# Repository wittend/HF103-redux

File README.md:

# NOTE: Just testing this REPO right now. - It may not work correctly!!
# HF103-redux
### A rework of an HF SDR using USB3 derived from a design developed by Oskar Stella, IK1XPV.
This variant is meant as a straw-man starting point for discussion of project options by members of the HamSCI and TAPR groups for scientific data-collection applications.  

It is a re-capture of design elements drawn from  Oskar's HF103, BBRF103, and other sources into a schematic drawn in KiCad.

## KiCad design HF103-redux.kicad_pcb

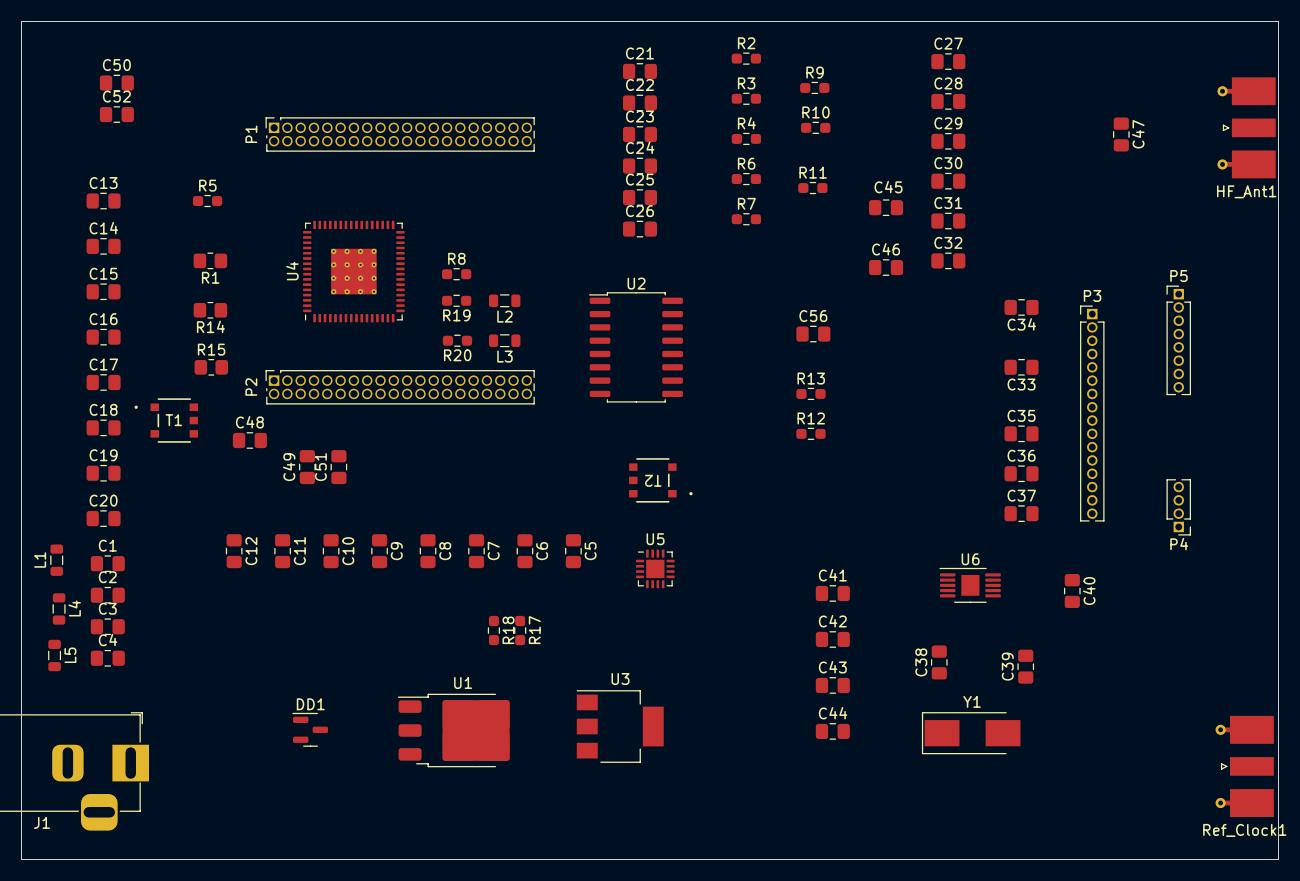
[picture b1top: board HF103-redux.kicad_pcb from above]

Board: 2 copper layers, 120.0 x 80.0 mm, 95 parts (0 on the bottom side), 75 nets, no tracks yet.

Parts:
C1, C4: 56pF; C_0805_2012Metric_Pad1.18x1.45mm_HandSolder
C2, C3: 150pF; C_0805_2012Metric_Pad1.18x1.45mm_HandSolder
C5, C6, C10, C11, C47: 100nF; C_0805_2012Metric_Pad1.18x1.45mm_HandSolder
C7, C8, C12: 1uF; C_0805_2012Metric_Pad1.18x1.45mm_HandSolder
C9: 10uF; C_0805_2012Metric_Pad1.18x1.45mm_HandSolder
C13, C14, C15, C16, C17, C18, C19, C20: C; C_0805_2012Metric_Pad1.18x1.45mm_HandSolder
C21, C22, C23, C24, C25, C26, C27, C28, C29, C30, C31, C32, C33, C34, C35, C36, C37, C42, C44, C46: 100pf; C_0805_2012Metric_Pad1.18x1.45mm_HandSolder
C38, C39: ? pF; C_0805_2012Metric_Pad1.18x1.45mm_HandSolder
C40: 1 nF; C_0805_2012Metric_Pad1.18x1.45mm_HandSolder
C41, C43, C45, C52, C56: 100nf; C_0805_2012Metric_Pad1.18x1.45mm_HandSolder
C48, C49: 8p2; C_0805_2012Metric_Pad1.18x1.45mm_HandSolder
C50: 10nf; C_0805_2012Metric_Pad1.18x1.45mm_HandSolder
C51: 4p2; C_0805_2012Metric_Pad1.18x1.45mm_HandSolder
DD1: BAV99; SOT-23
HF_Ant1: Conn_Coaxial; SMA_Molex_73251-2120_EdgeMount_Horizontal
J1: Barrel_Jack; BarrelJack_Horizontal
L1, L5: 390nH; L_0805_2012Metric
L2, L3: 68nH; L_0805_2012Metric
L4: 470nH; L_0805_2012Metric
P1, P2: Conn_02x20_Odd_Even; PinSocket_2x20_P1.27mm_Vertical
P3: Conn_01x16; PinHeader_1x16_P1.27mm_Vertical
P4: Conn_01x04; PinHeader_1x04_P1.27mm_Vertical
P5: Conn_01x08; PinHeader_1x08_P1.27mm_Vertical
R1, R14, R15: 100; R_0805_2012Metric_Pad1.20x1.40mm_HandSolder
R2, R4, R5, R6, R7, R8, R9, R10, R11: 1k; R_0603_1608Metric_Pad0.98x0.95mm_HandSolder
R3: 10k; R_0603_1608Metric_Pad0.98x0.95mm_HandSolder
R12, R13: 100; R_0603_1608Metric_Pad0.98x0.95mm_HandSolder
R17, R18, R19, R20: TBD; R_0603_1608Metric_Pad0.98x0.95mm_HandSolder
Ref_Clock1: Conn_Coaxial; SMA_Molex_73251-2120_EdgeMount_Horizontal
T1, T2: ETC1-1T-2TR; ETC1-1-13TR_MCM
U1: AMS1117CD-1.8; TO-252-3_TabPin2
U2: 74CBTLV3253; SO-16_5.3x10.2mm_P1.27mm
U3: AP7361C-33E; SOT-223-3_TabPin2
U4: LTC2208CUP-14-PBF; QFN-64-1EP_9x9mm_P0.5mm_EP4.35x4.35mm_ThermalVias
U5: LTC6400CUD-20-PBF; QFN-16-1EP_3x3mm_P0.5mm_EP1.75x1.75mm
U6: SI5351A-B-GT; MSOP-10-1EP_3x3mm_P0.5mm_EP1.73x1.98mm
Y1: 27 MHz; Crystal_SMD_0603-2Pin_6.0x3.5mm_HandSoldering

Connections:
+1V8: C6.1, C7.1, U1.2 (VO)
AIN+: R19.1, U4.8 (AIN+)
AIN-: R20.1, U4.9 (AIN-)
ATT CLK: C32.1, R6.2
ATT DATA: C31.1, R7.2
ATT LE: C33.1, P3.8, R4.2
CLK0: C51.2, U6.10 (CLK0)
D0: P2.38, U4.44 (D7+/DA0)
D1: P2.36, U4.45 (D8-/DA1)
D2: P2.34, U4.46 (D8+/DA2)
D3: P2.32, U4.47 (D9-/DA3)
D4: P2.30, U4.48 (D9+/DA4)
D5: P2.28, U4.51 (D10-/DA5)
D6: P2.26, U4.52 (D10+/DA6)
D7: P2.24, U4.53 (D11-/DA7)
D8: P2.22, U4.54 (D11+/DA8)
D9: P2.20, U4.55 (D12-/DA9)
D10: P2.18, U4.56 (D12+/DA10)
D11: P2.16, U4.57 (D13-/DA11)
D12: P2.14, U4.58 (D13+/DA12)
D13: P2.12, U4.59 (OF-/DA13)
GND: C1.2, C2.2, C3.2, C4.2, C5.2, C6.2, C7.2, C8.2, C9.2, C10.2, C11.2, C12.2, C13.2, C14.2, C15.2, C16.2, C17.2, C18.2, C19.2, C20.2, C21.2, C22.2, C23.2, C24.2, C25.2, C26.2, C27.2, C28.2, C29.2, C30.2, C31.2, C32.2, C33.2, C34.2, C35.2, C36.2, C37.2, C38.1, C39.2, C40.1, C41.1, C42.1, C43.1, C44.1, C45.1, C46.1, C49.1, C50.1, C52.1, C56.2, DD1.1 (K), HF_Ant1.2 (Ext), J1.2, P1.39, P1.40, P2.5, P2.6, P2.33, P2.37, P3.11, P3.14, P4.4, P5.1, Ref_Clock1.2 (Ext), T1.5, T2.5, U1.1 (GND), U2.1 (1~OE), U2.8 (GND), U2.15 (2~OE), U3.2 (GND), U4.2 (GND), U4.4 (GND), U4.7 (GND), U4.10 (GND), U4.11 (GND), U4.14 (GND), U4.18 (GND), U4.61 (LVDS), U5.4 (V-), U5.9 (V-), U5.11 (*ENABLE), U5.12 (V-), U5.17 (EPAD), U6.8 (GND)
GPIO17: P2.31, U4.20 (DITH)
GPIO18: P2.29, U4.19 (SHDN)
GPIO19: P2.27, R2.1
GPIO20: P2.25, R3.1
GPIO21: P2.23, R4.1
GPIO22: P2.21, R6.1
GPIO23: P2.19, R7.1
GPIO24: P2.17, R8.1
GPIO25: P2.15, R9.1
GPIO26: P2.13, R10.1, U2.14 (S0)
GPIO27: P2.11, R11.1, U2.2 (S1)
GPIO28: P2.9, U4.60 (OF+/0FA)
GPIO29: P2.7, U4.63 (RAND)
I2C SCL: P2.40, R12.1, U6.4 (SCL)
I2C SDA: P2.39, R13.1, U6.5 (SDA)
IOVDD: C18.1, C20.1
unnamed: C2.1, L1.1, L4.1
unnamed: C3.1, L4.2, L5.1
unnamed: C4.1, L5.2, T2.4
unnamed: C49.2, R14.2, R15.1, T1.2
unnamed: C50.2, C52.2, T2.2
unnamed: C51.1, T1.4
unnamed: C47.1, HF_Ant1.1 (In)
unnamed: L2.1, R18.1
unnamed: L2.2, R19.2
unnamed: L3.1, R17.1
unnamed: L3.2, R20.2
unnamed: P2.3, P2.4
unnamed: C22.1, C27.1, P3.2, P5.3, R11.2
unnamed: C24.1, C28.1, P3.3, P5.4, R10.2
unnamed: C21.1, C25.1, C29.1, C30.1, P3.4, P3.5, P5.5, P5.6, R8.2, R9.2
unnamed: C23.1, C34.1, P3.9, P5.7, R3.2
unnamed: C26.1, C35.1, P3.10, P5.8, R2.2
unnamed: C36.1, P3.15, P4.1, R13.2
unnamed: C37.1, P3.16, P4.2, R12.2
unnamed: T2.1, U5.13 (+IN), U5.14 (+IN)
unnamed: T2.3, U5.15 (-IN), U5.16 (-IN)
unnamed: C1.1, L1.2, U2.7 (1A)
unnamed: C47.2, DD1.3 (K), U2.9 (2A)
unnamed: C48.1, R1.1, R14.1, T1.1, U4.12 (ENC+)
unnamed: C48.2, R1.2, R15.2, T1.3, U4.13 (ENC-)
unnamed: R5.2, U4.62 (MODE)
unnamed: R17.2, U5.8 (+OUT)
unnamed: R18.2, U5.5 (-OUT)
unnamed: C40.2, U6.7 (VDDO)
PCLK: P2.35, U4.41 (D6-/CLKOUTA)
REF CLK: Ref_Clock1.1 (In), U6.6 (CLK2)
VC6400: C41.2, C42.2, C43.2, C44.2, C45.2, C46.2, U5.1 (V+), U5.3 (V+), U5.10 (V+)
VCC: C9.1, C10.1, J1.1, U3.1 (VI)
VCM: U4.3 (VCM), U5.2 (VOCM)
VDD: C5.1, C8.1, C11.1, C12.1, C13.1, C14.1, C15.1, C16.1, C17.1, C19.1, C56.1, DD1.2 (A), R5.1, U1.3 (VI), U2.16 (VCC), U3.3 (VO), U4.1 (SENSE), U4.5 (VDD), U4.6 (VDD), U4.15 (VDD), U4.16 (VDD), U4.17 (VDD), U6.1 (VDD)
XA: C39.1, U6.2 (XA), Y1.2
XB: C38.2, U6.3 (XB), Y1.1

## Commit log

2023-07-15 Initial upload of KiCad project
2023-07-16 Adding progress and design notes.
2023-07-16 Updated schematic PDF 2023-07-16
2023-07-17 Update PDF
2023-07-19 Add most recent 'Notes' .pdf
2023-07-19 Commit latest schematic changes
2023-07-19 Add other project files
